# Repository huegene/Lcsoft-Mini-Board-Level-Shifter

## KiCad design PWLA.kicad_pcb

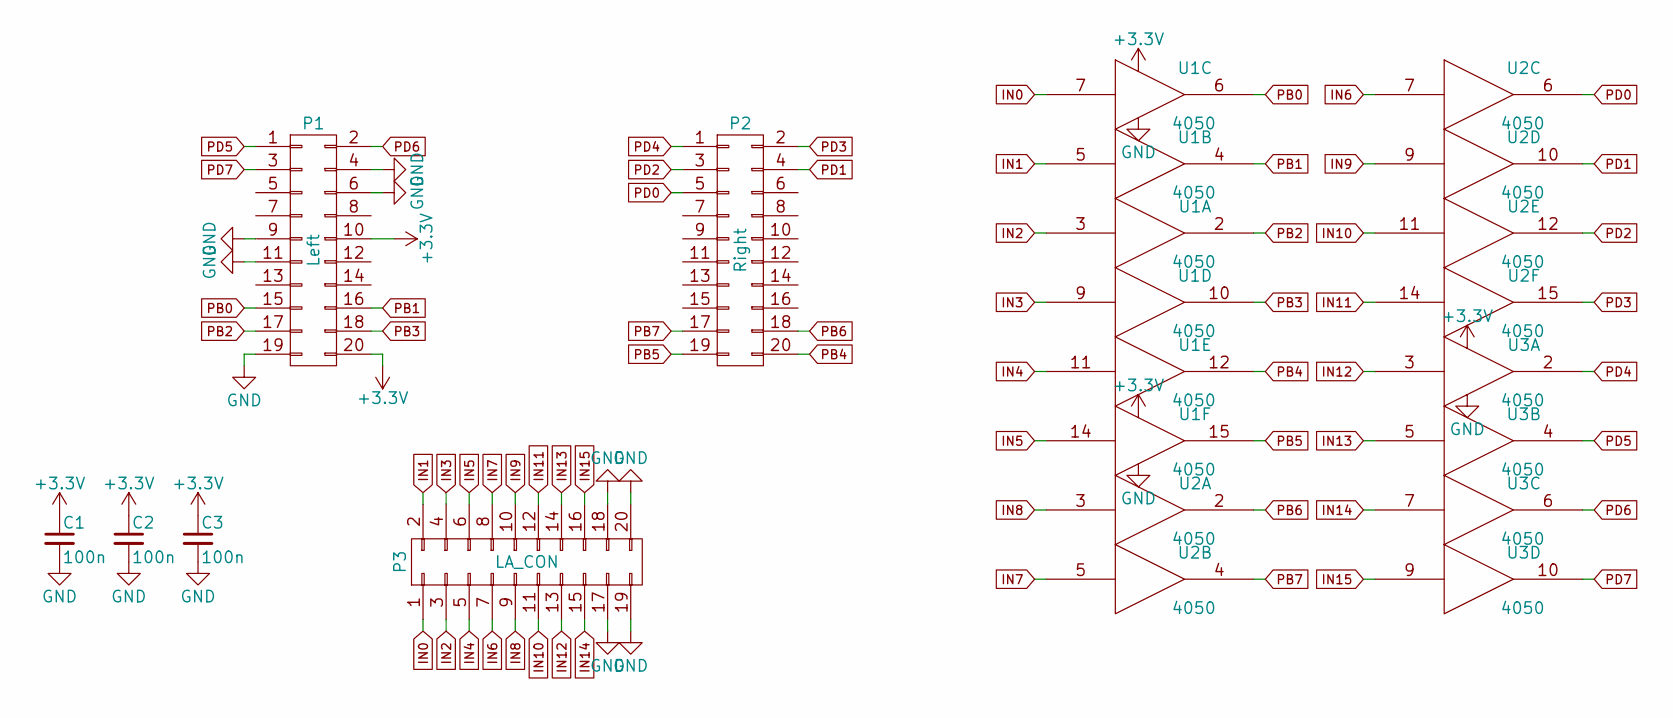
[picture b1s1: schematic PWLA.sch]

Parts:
C1, C2, C3: 100n; C_0603_HandSoldering
P1: Left; Pin_Header_Straight_2x10_Pitch2.54mm
P2: Right; Pin_Header_Straight_2x10_Pitch2.54mm
P3: LA_CON; con-amp-micromatch-MMT-SMD-20
U1, U2, U3: 4050; SOIC-16_3.9x9.9mm_Pitch1.27mm

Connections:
+3V3: C1.1, C2.1, C3.1, P1.10, P1.20, U1.1 (VCC), U2.1 (VCC), U3.1 (VCC)
GND: C1.2, C2.2, C3.2, P1.4, P1.6, P1.9, P1.11, P1.19, P3.17, P3.18, P3.19, P3.20, U1.8 (VSS), U2.8 (VSS), U3.8 (VSS)
IN0: P3.1, U1.7
IN1: P3.2, U1.5
IN2: P3.3, U1.3
IN3: P3.4, U1.9
IN4: P3.5, U1.11
IN5: P3.6, U1.14
IN6: P3.7, U2.7
IN7: P3.8, U2.5
IN8: P3.9, U2.3
IN9: P3.10, U2.9
IN10: P3.11, U2.11
IN11: P3.12, U2.14
IN12: P3.13, U3.3
IN13: P3.14, U3.5
IN14: P3.15, U3.7
IN15: P3.16, U3.9
PB0: P1.15, U1.6
PB1: P1.16, U1.4
PB2: P1.17, U1.2
PB3: P1.18, U1.10
PB4: P2.20, U1.12
PB5: P2.19, U1.15
PB6: P2.18, U2.2
PB7: P2.17, U2.4
PD0: P2.5, U2.6
PD1: P2.4, U2.10
PD2: P2.3, U2.12
PD3: P2.2, U2.15
PD4: P2.1, U3.2
PD5: P1.1, U3.4
PD6: P1.2, U3.6
PD7: P1.3, U3.10

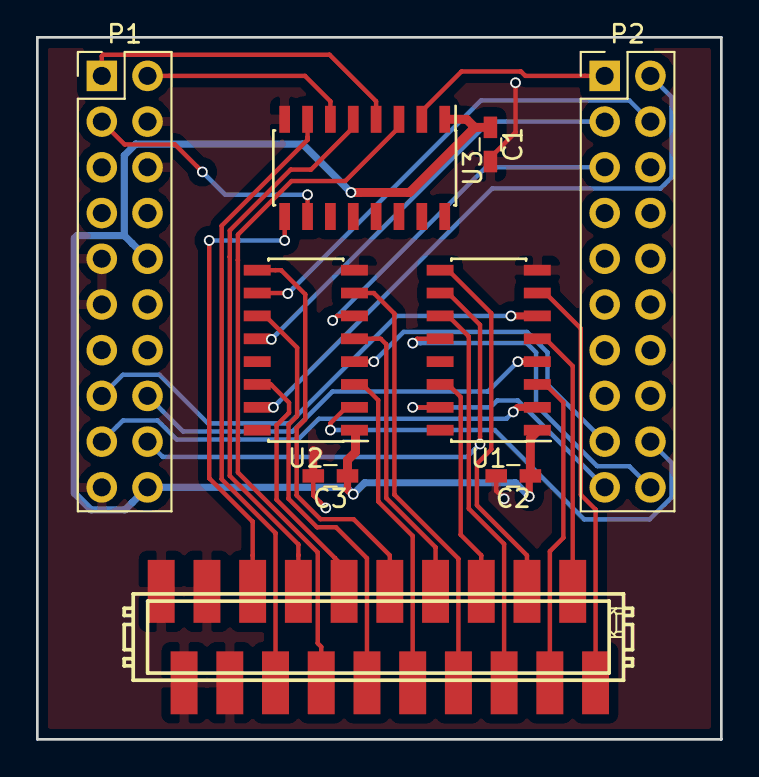
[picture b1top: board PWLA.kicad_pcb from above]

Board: 2 copper layers, 38.0 x 39.0 mm, 9 parts (0 on the bottom side), 34 nets.

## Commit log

2019-04-19 initial commit v0.0.1
2019-04-19 added unzipped files
